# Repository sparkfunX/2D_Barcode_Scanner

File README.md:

2D Barcode Scanner Breakout
========================================

[*2D Barcode Scanner Breakout (SPX-16441)*](https://www.sparkfun.com/products/16441)

The DYScan DE2120 is one of the coolest little barcode scanners we've ever seen. This tiny "scan engine" will read 20 different barcode symbologies — both 1D and 2D! This is achieved by using a camera coupled with on-board image processing to identify and decode everything from UPC codes to QR codes. The module also features two LEDs: one for illumination and one to project the red line that you're used to seeing from laser-based scanners. 

This breakout board makes it easy to explore all of the capabilities of the DE2120 without dealing with finicky flat flex cables. The scanner's USB interface is exposed via the on-board USB-C connector. A buzzer and status LED are connected to the module through appropriate drive circuits and a pushbutton tactile switch is provided on the "trigger" pin. When you're ready to incorporate the module into your embedded project, you can leverage the 5 pin header for direct access to the TTL serial pins, power pins, and trigger input.

The module can be configured either by using the serial interface or by scanning command barcodes found in the datasheet.

Repository Contents
-------------------
* **/Hardware** - Eagle design files (.brd, .sch)

Documentation
--------------
* [Schematic](https://cdn.sparkfun.com/assets/3/8/9/6/0/2D_Barcode_Scanner.pdf)
* [Datasheet](https://cdn.sparkfun.com/assets/6/4/6/1/f/DY_SCAN_Specification-DE2120_1___2_.pdf)
* [Settings Manual](https://cdn.sparkfun.com/assets/b/5/0/e/e/DY_Scan_Setting_Manual-DE2120___19.4.6___.pdf)
* [Eagle Files](https://cdn.sparkfun.com/assets/2/d/f/7/b/2DBarcodeScanner.zip)

License Information
-------------------

This product is _**open source**_! 

Please review the LICENSE.md file for license information. 

If you have any questions or concerns on licensing, please contact technical support on our [SparkFun forums](https://forum.sparkfun.com/viewforum.php?f=152).

Distributed as-is; no warranty is given.

- Your friends at SparkFun.

_<COLLABORATION CREDIT>_

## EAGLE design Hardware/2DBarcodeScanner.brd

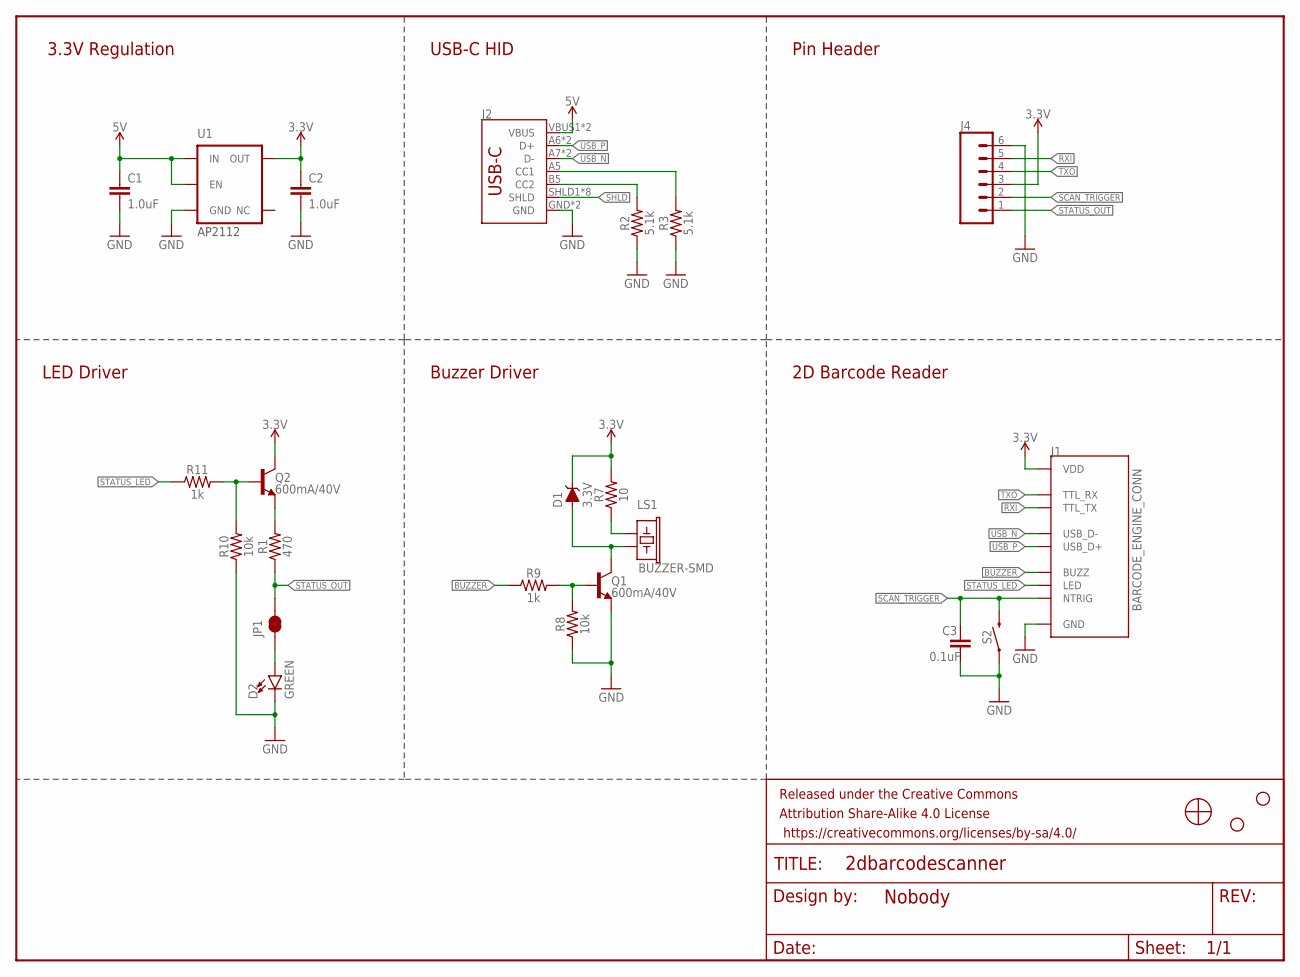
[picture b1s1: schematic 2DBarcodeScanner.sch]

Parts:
C1, C2: 1.0uF; 0603
C3: 0.1uF; 0603
D1: 3.3V; SOD-323
D2: GREEN; LED-0603
FRAME1: FRAME-LETTERNO_PACKAGE; DUMMY
H2, H3: STAND-OFF
J1: BARCODE_ENGINE_CONN; CONN_FPC_BOTTOM_12POS_.5MM_R/A
J2: USB_C2-LAYER; USB-C-16P
J4: CONN_06NO_SILK_FEMALE_PTH; 1X06_NO_SILK
JP1: JUMPER-SMT_2_NC_TRACE_SILK; SMT-JUMPER_2_NC_TRACE_SILK
LS1: BUZZER-SMD; BUZZER-CCV
Q1, Q2: 600mA/40V; SOT23-3
R1: 470; 0603
R2, R3: 5.1k; 0603
R7: 10; 0603
R8, R10: 10k; 0603
R9, R11: 1k; 0603
S2: MOMENTARY-SWITCH-SPST-SMD-5.2MM-TALL; TACTILE_SWITCH_SMD_5.2MM
U1: 3.3V; SOT23-5
U$1: BARCODE_SCANNER_MOUNT

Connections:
3.3V: C2.1, D1.C, J1.P$11 (VDD), J4.3, Q2.3 (C), R7.2, U1.5 (OUT)
5V: C1.1, J2.VBUS1 (VBUS), J2.VBUS2 (VBUS), U1.1 (IN), U1.3 (EN)
BUZZER: J1.P$4 (BUZZ), R9.1
CC3: J2.A5 (CC1), R3.2
CC4: J2.B5 (CC2), R2.2
GND: C1.2, C2.2, C3.2, D2.C, J1.P$10 (GND), J1.P$13 (GND), J1.P$14 (GND), J2.GND, J2.GND2 (GND), J4.6, Q1.2 (E), R2.1, R3.1, R8.1, R10.1, S2.1, U1.2 (GND)
unnamed: D1.A, LS1.- (2), Q1.3 (C)
unnamed: LS1.+ (1), R7.1
unnamed: Q2.2 (E), R1.2
unnamed: Q1.1 (B), R8.2, R9.2
unnamed: Q2.1 (B), R10.2, R11.2
unnamed: D2.A, JP1.1
RXI: J1.P$8 (TTL_TX), J4.5
SCAN_TRIGGER: C3.1, J1.P$1 (NTRIG), J4.2, S2.3 (2)
SHLD: J2.SHLD1 (SHLD), J2.SHLD2 (SHLD), J2.SHLD3 (SHLD), J2.SHLD4 (SHLD), J2.SHLD5 (SHLD), J2.SHLD6 (SHLD), J2.SHLD7 (SHLD), J2.SHLD8 (SHLD)
STATUS_LED: J1.P$3 (LED), R11.1
STATUS_OUT: J4.1, JP1.2, R1.1
TXO: J1.P$9 (TTL_RX), J4.4
USB_N: J1.P$7 (USB_D-), J2.A7 (D-), J2.B7 (D-)
USB_P: J1.P$6 (USB_D+), J2.A6 (D+), J2.B6 (D+)

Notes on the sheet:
3.3V Regulation
AP2112
Pin Header
2D Barcode Reader
LED Driver
Buzzer Driver
USB-C HID

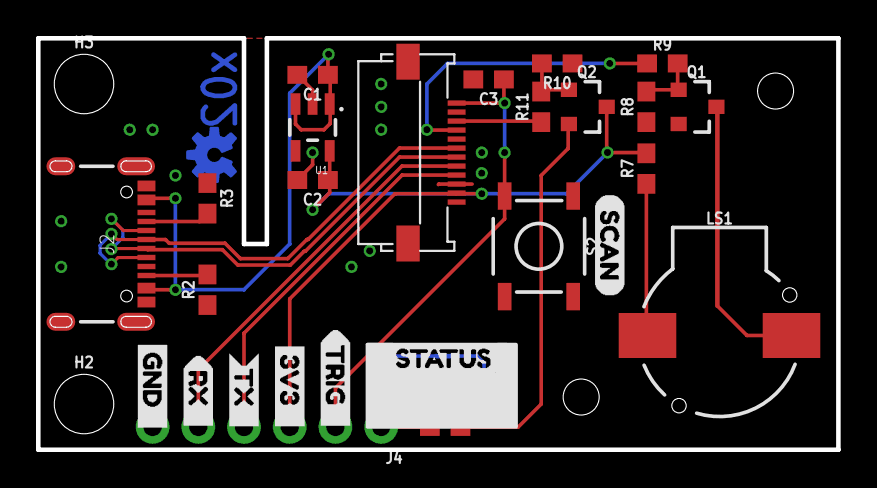
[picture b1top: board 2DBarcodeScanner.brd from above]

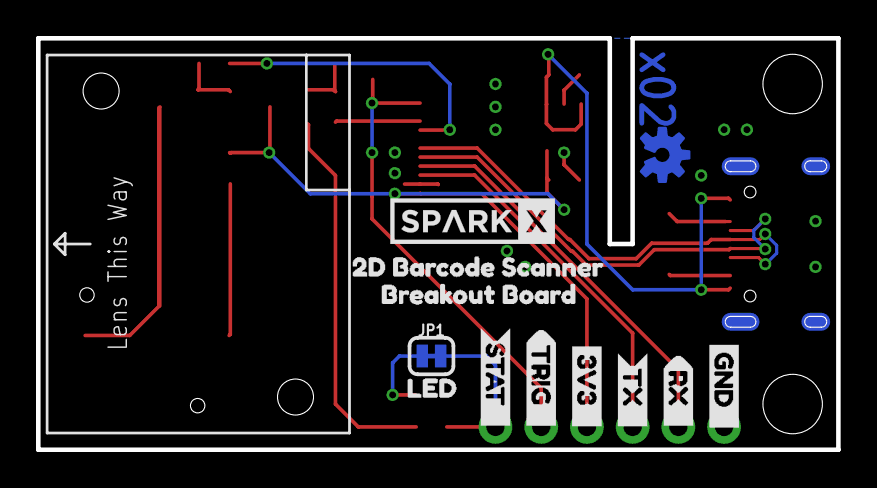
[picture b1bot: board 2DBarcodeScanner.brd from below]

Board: 2 copper layers, 44.5 x 22.9 mm, 43 parts (13 on the bottom side), 20 nets.

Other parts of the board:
U$2: STATUS3
U$3: STAT__5
U$4, U$5: TRIG__4
U$6, U$9: 3V3__3
U$7: SCAN4
U$8: LED0
U$10, U$11: TX__2
U$12, U$13: RX__1
U$14, U$15: GND__0
U$17: 2D_BARCODE_SCANNER0
U$18: BREAKOUT_BOARD1
U$20: SPARKX-MEDIUM
U$21: OSHW-LOGO-S_COPPER

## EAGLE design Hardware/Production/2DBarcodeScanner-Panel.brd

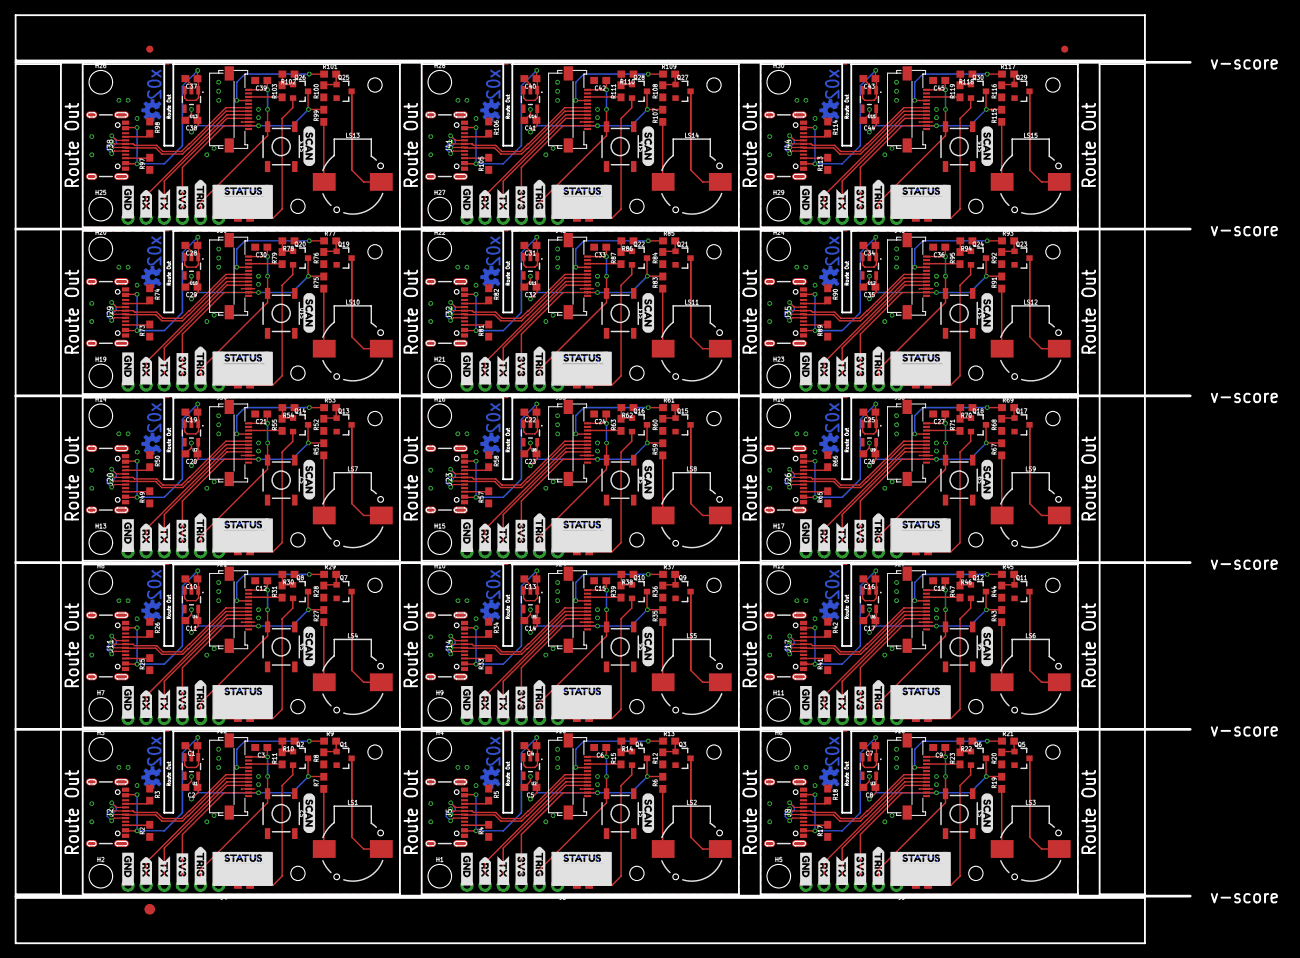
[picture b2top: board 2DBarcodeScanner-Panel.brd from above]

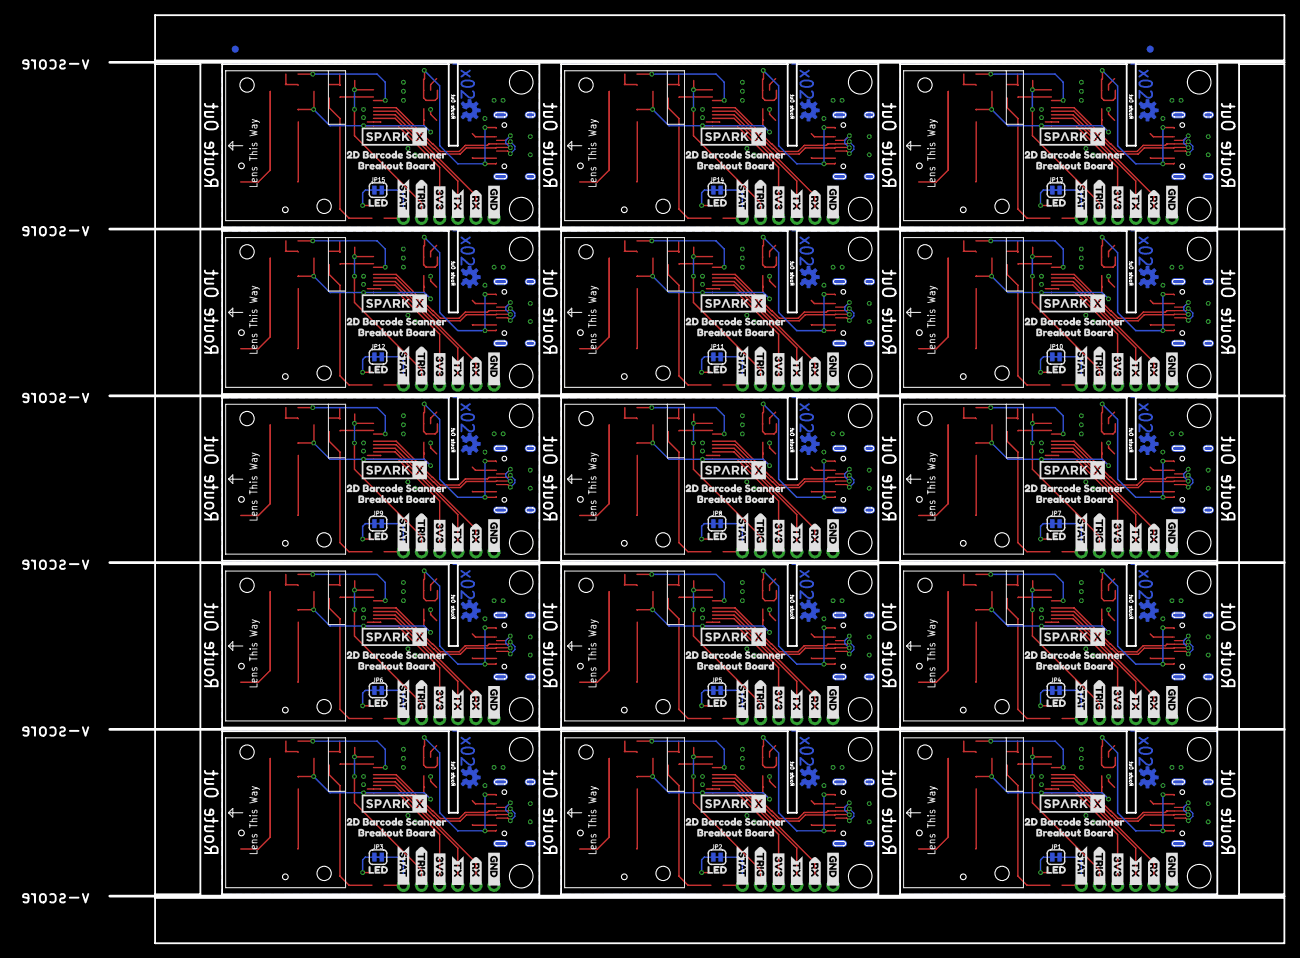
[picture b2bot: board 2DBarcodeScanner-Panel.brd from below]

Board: 2 copper layers, 177.8 x 129.9 mm, 650 parts (197 on the bottom side), 300 nets.

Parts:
C1, C2, C4, C5, C7, C8, C10, C11, C13, C14, C16, C17, C19, C20, C22, C23, C25, C26, C28, C29, C31, C32, C34, C35, C37, C38, C40, C41, C43, C44: 1.0uF; 0603
C3, C6, C9, C12, C15, C18, C21, C24, C27, C30, C33, C36, C39, C42, C45: 0.1uF; 0603
D1, D2, D3, D4, D5, D6, D7, D8, D9, D10, D11, D12, D13, D14, D15: GREEN; LED-0603
E$1, E$2, E$3, E$4: FIDUCIAL-1X2
E$5: FIDUCIAL-1.5X3
FRAME1, FRAME2, FRAME3, FRAME4, FRAME5, FRAME6, FRAME7, FRAME8, FRAME9, FRAME10, FRAME11, FRAME12, FRAME13, FRAME14, FRAME15: FRAME-LETTERNO_PACKAGE; DUMMY
H1, H2, H3, H4, H5, H6, H7, H8, H9, H10, H11, H12, H13, H14, H15, H16, H17, H18, H19, H20, H21, H22, H23, H24, H25, H26, H27, H28, H29, H30: STAND-OFF
J1, J3, J7, J10, J13, J16, J19, J22, J25, J28, J31, J34, J37, J40, J43: BARCODE_ENGINE_CONN; CONN_FPC_BOTTOM_12POS_.5MM_R/A
J2, J5, J8, J11, J14, J17, J20, J23, J26, J29, J32, J35, J38, J41, J44: USB-C-16P
J4, J6, J9, J12, J15, J18, J21, J24, J27, J30, J33, J36, J39, J42, J45: 1X06_NO_SILK
JP1, JP2, JP3, JP4, JP5, JP6, JP7, JP8, JP9, JP10, JP11, JP12, JP13, JP14, JP15: JUMPER-SMT_2_NC_TRACE_SILK; SMT-JUMPER_2_NC_TRACE_SILK
LS1, LS2, LS3, LS4, LS5, LS6, LS7, LS8, LS9, LS10, LS11, LS12, LS13, LS14, LS15: BUZZER-SMD; BUZZER-CCV
Q1, Q2, Q3, Q4, Q5, Q6, Q7, Q8, Q9, Q10, Q11, Q12, Q13, Q14, Q15, Q16, Q17, Q18, Q19, Q20, Q21, Q22, Q23, Q24, Q25, Q26, Q27, Q28, Q29, Q30: 600mA/40V; SOT23-3
R1, R16, R24, R32, R40, R48, R56, R64, R72, R80, R88, R96, R104, R112, R120: 470; 0603
R2, R3, R4, R5, R17, R18, R25, R26, R33, R34, R41, R42, R49, R50, R57, R58, R65, R66, R73, R74, R81, R82, R89, R90, R97, R98, R105, R106, R113, R114: 5.1k; 0603
R6, R7, R19, R27, R35, R43, R51, R59, R67, R75, R83, R91, R99, R107, R115: 10; 0603
R8, R10, R12, R14, R20, R22, R28, R30, R36, R38, R44, R46, R52, R54, R60, R62, R68, R70, R76, R78, R84, R86, R92, R94, R100, R102, R108, R110, R116, R118: 10k; 0603
R9, R11, R13, R15, R21, R23, R29, R31, R37, R39, R45, R47, R53, R55, R61, R63, R69, R71, R77, R79, R85, R87, R93, R95, R101, R103, R109, R111, R117, R119: 1k; 0603
S1, S2, S3, S4, S5, S6, S7, S8, S9, S10, S11, S12, S13, S14, S15: MOMENTARY-SWITCH-SPST-SMD-5.2MM-TALL; TACTILE_SWITCH_SMD_5.2MM
U1, U2, U3, U4, U5, U6, U7, U8, U9, U10, U11, U12, U13, U14, U15: 3.3V; SOT23-5
U$1, U$16, U$39, U$58, U$77, U$96, U$115, U$134, U$153, U$172, U$191, U$210, U$229, U$248, U$267: BARCODE_SCANNER_MOUNT
U$2, U$37, U$56, U$75, U$94, U$113, U$132, U$151, U$170, U$189, U$208, U$227, U$246, U$265, U$284: STATUS3
U$3, U$26, U$45, U$64, U$83, U$102, U$121, U$140, U$159, U$178, U$197, U$216, U$235, U$254, U$273: STAT__5
U$4, U$5, U$27, U$28, U$46, U$47, U$65, U$66, U$84, U$85, U$103, U$104, U$122, U$123, U$141, U$142, U$160, U$161, U$179, U$180, U$198, U$199, U$217, U$218, U$236, U$237, U$255, U$256, U$274, U$275: TRIG__4
U$6, U$9, U$29, U$30, U$48, U$49, U$67, U$68, U$86, U$87, U$105, U$106, U$124, U$125, U$143, U$144, U$162, U$163, U$181, U$182, U$200, U$201, U$219, U$220, U$238, U$239, U$257, U$258, U$276, U$277: 3V3__3
U$7, U$19, U$40, U$59, U$78, U$97, U$116, U$135, U$154, U$173, U$192, U$211, U$230, U$249, U$268: SCAN4
U$8, U$38, U$57, U$76, U$95, U$114, U$133, U$152, U$171, U$190, U$209, U$228, U$247, U$266, U$285: LED0
U$10, U$11, U$31, U$32, U$50, U$51, U$69, U$70, U$88, U$89, U$107, U$108, U$126, U$127, U$145, U$146, U$164, U$165, U$183, U$184, U$202, U$203, U$221, U$222, U$240, U$241, U$259, U$260, U$278, U$279: TX__2
U$12, U$13, U$33, U$34, U$52, U$53, U$71, U$72, U$90, U$91, U$109, U$110, U$128, U$129, U$147, U$148, U$166, U$167, U$185, U$186, U$204, U$205, U$223, U$224, U$242, U$243, U$261, U$262, U$280, U$281: RX__1
U$14, U$15, U$35, U$36, U$54, U$55, U$73, U$74, U$92, U$93, U$111, U$112, U$130, U$131, U$149, U$150, U$168, U$169, U$187, U$188, U$206, U$207, U$225, U$226, U$244, U$245, U$263, U$264, U$282, U$283: GND__0
U$17, U$22, U$41, U$60, U$79, U$98, U$117, U$136, U$155, U$174, U$193, U$212, U$231, U$250, U$269: 2D_BARCODE_SCANNER0
U$18, U$23, U$42, U$61, U$80, U$99, U$118, U$137, U$156, U$175, U$194, U$213, U$232, U$251, U$270: BREAKOUT_BOARD1
U$20, U$24, U$43, U$62, U$81, U$100, U$119, U$138, U$157, U$176, U$195, U$214, U$233, U$252, U$271: SPARKX-MEDIUM
U$21, U$25, U$44, U$63, U$82, U$101, U$120, U$139, U$158, U$177, U$196, U$215, U$234, U$253, U$272: OSHW-LOGO-S_COPPER

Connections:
3.3V: C2.1, J1.P$11, J4.3, Q2.3, R7.2, U1.5
3.3V1: C5.1, J3.P$11, J6.3, Q4.3, R6.2, U2.5
3.3V2: C8.1, J7.P$11, J9.3, Q6.3, R19.2, U3.5
3.3V3: C11.1, J10.P$11, J12.3, Q8.3, R27.2, U4.5
3.3V4: C14.1, J13.P$11, J15.3, Q10.3, R35.2, U5.5
3.3V5: C17.1, J16.P$11, J18.3, Q12.3, R43.2, U6.5
3.3V6: C20.1, J19.P$11, J21.3, Q14.3, R51.2, U7.5
3.3V7: C23.1, J22.P$11, J24.3, Q16.3, R59.2, U8.5
3.3V8: C26.1, J25.P$11, J27.3, Q18.3, R67.2, U9.5
3.3V9: C29.1, J28.P$11, J30.3, Q20.3, R75.2, U10.5
3.3V10: C32.1, J31.P$11, J33.3, Q22.3, R83.2, U11.5
3.3V11: C35.1, J34.P$11, J36.3, Q24.3, R91.2, U12.5
3.3V12: C38.1, J37.P$11, J39.3, Q26.3, R99.2, U13.5
3.3V13: C41.1, J40.P$11, J42.3, Q28.3, R107.2, U14.5
3.3V14: C44.1, J43.P$11, J45.3, Q30.3, R115.2, U15.5
5V: C1.1, J2.VBUS1, J2.VBUS2, U1.1, U1.3
5V1: C4.1, J5.VBUS1, J5.VBUS2, U2.1, U2.3
5V2: C7.1, J8.VBUS1, J8.VBUS2, U3.1, U3.3
5V3: C10.1, J11.VBUS1, J11.VBUS2, U4.1, U4.3
5V4: C13.1, J14.VBUS1, J14.VBUS2, U5.1, U5.3
5V5: C16.1, J17.VBUS1, J17.VBUS2, U6.1, U6.3
5V6: C19.1, J20.VBUS1, J20.VBUS2, U7.1, U7.3
5V7: C22.1, J23.VBUS1, J23.VBUS2, U8.1, U8.3
5V8: C25.1, J26.VBUS1, J26.VBUS2, U9.1, U9.3
5V9: C28.1, J29.VBUS1, J29.VBUS2, U10.1, U10.3
5V10: C31.1, J32.VBUS1, J32.VBUS2, U11.1, U11.3
5V11: C34.1, J35.VBUS1, J35.VBUS2, U12.1, U12.3
5V12: C37.1, J38.VBUS1, J38.VBUS2, U13.1, U13.3
5V13: C40.1, J41.VBUS1, J41.VBUS2, U14.1, U14.3
5V14: C43.1, J44.VBUS1, J44.VBUS2, U15.1, U15.3
BUZZER: J1.P$4, R9.1
BUZZER1: J3.P$4, R13.1
BUZZER2: J7.P$4, R21.1
BUZZER3: J10.P$4, R29.1
BUZZER4: J13.P$4, R37.1
BUZZER5: J16.P$4, R45.1
BUZZER6: J19.P$4, R53.1
BUZZER7: J22.P$4, R61.1
BUZZER8: J25.P$4, R69.1
BUZZER9: J28.P$4, R77.1
BUZZER10: J31.P$4, R85.1
BUZZER11: J34.P$4, R93.1
BUZZER12: J37.P$4, R101.1
BUZZER13: J40.P$4, R109.1
BUZZER14: J43.P$4, R117.1
CC1: J5.A5, R5.2
CC2: J5.B5, R4.2
CC3: J2.A5, R3.2
CC4: J2.B5, R2.2
CC5: J8.A5, R18.2
CC6: J8.B5, R17.2
CC7: J11.A5, R26.2
CC8: J11.B5, R25.2
CC9: J14.A5, R34.2
CC10: J14.B5, R33.2
CC11: J17.A5, R42.2
CC12: J17.B5, R41.2
CC13: J20.A5, R50.2
CC14: J20.B5, R49.2
CC15: J23.A5, R58.2
CC16: J23.B5, R57.2
CC17: J26.A5, R66.2
CC18: J26.B5, R65.2
CC19: J29.A5, R74.2
CC20: J29.B5, R73.2
CC21: J32.A5, R82.2
CC22: J32.B5, R81.2
CC23: J35.A5, R90.2
CC24: J35.B5, R89.2
CC25: J38.A5, R98.2
CC26: J38.B5, R97.2
CC27: J41.A5, R106.2
CC28: J41.B5, R105.2
CC29: J44.A5, R114.2
CC30: J44.B5, R113.2
GND: C1.2, C2.2, C3.2, D2.C, J1.P$10, J1.P$13, J1.P$14, J2.GND, J2.GND2, J4.6, Q1.2, R2.1, R3.1, R8.1, R10.1, S2.1, U1.2
GND1: C4.2, C5.2, C6.2, D1.C, J3.P$10, J3.P$13, J3.P$14, J5.GND, J5.GND2, J6.6, Q3.2, R4.1, R5.1, R12.1, R14.1, S1.1, U2.2
GND2: C7.2, C8.2, C9.2, D3.C, J7.P$10, J7.P$13, J7.P$14, J8.GND, J8.GND2, J9.6, Q5.2, R17.1, R18.1, R20.1, R22.1, S3.1, U3.2
GND3: C10.2, C11.2, C12.2, D4.C, J10.P$10, J10.P$13, J10.P$14, J11.GND, J11.GND2, J12.6, Q7.2, R25.1, R26.1, R28.1, R30.1, S4.1, U4.2
GND4: C13.2, C14.2, C15.2, D5.C, J13.P$10, J13.P$13, J13.P$14, J14.GND, J14.GND2, J15.6, Q9.2, R33.1, R34.1, R36.1, R38.1, S5.1, U5.2
GND5: C16.2, C17.2, C18.2, D6.C, J16.P$10, J16.P$13, J16.P$14, J17.GND, J17.GND2, J18.6, Q11.2, R41.1, R42.1, R44.1, R46.1, S6.1, U6.2
GND6: C19.2, C20.2, C21.2, D7.C, J19.P$10, J19.P$13, J19.P$14, J20.GND, J20.GND2, J21.6, Q13.2, R49.1, R50.1, R52.1, R54.1, S7.1, U7.2
GND7: C22.2, C23.2, C24.2, D8.C, J22.P$10, J22.P$13, J22.P$14, J23.GND, J23.GND2, J24.6, Q15.2, R57.1, R58.1, R60.1, R62.1, S8.1, U8.2
GND8: C25.2, C26.2, C27.2, D9.C, J25.P$10, J25.P$13, J25.P$14, J26.GND, J26.GND2, J27.6, Q17.2, R65.1, R66.1, R68.1, R70.1, S9.1, U9.2
GND9: C28.2, C29.2, C30.2, D10.C, J28.P$10, J28.P$13, J28.P$14, J29.GND, J29.GND2, J30.6, Q19.2, R73.1, R74.1, R76.1, R78.1, S10.1, U10.2
GND10: C31.2, C32.2, C33.2, D11.C, J31.P$10, J31.P$13, J31.P$14, J32.GND, J32.GND2, J33.6, Q21.2, R81.1, R82.1, R84.1, R86.1, S11.1, U11.2
GND11: C34.2, C35.2, C36.2, D12.C, J34.P$10, J34.P$13, J34.P$14, J35.GND, J35.GND2, J36.6, Q23.2, R89.1, R90.1, R92.1, R94.1, S12.1, U12.2
GND12: C37.2, C38.2, C39.2, D13.C, J37.P$10, J37.P$13, J37.P$14, J38.GND, J38.GND2, J39.6, Q25.2, R97.1, R98.1, R100.1, R102.1, S13.1, U13.2
GND13: C40.2, C41.2, C42.2, D14.C, J40.P$10, J40.P$13, J40.P$14, J41.GND, J41.GND2, J42.6, Q27.2, R105.1, R106.1, R108.1, R110.1, S14.1, U14.2
GND14: C43.2, C44.2, C45.2, D15.C, J43.P$10, J43.P$13, J43.P$14, J44.GND, J44.GND2, J45.6, Q29.2, R113.1, R114.1, R116.1, R118.1, S15.1, U15.2
unnamed: LS2.-, Q3.3
unnamed: LS1.-, Q1.3
unnamed: LS1.+, R7.1
unnamed: Q2.2, R1.2
unnamed: Q1.1, R8.2, R9.2
unnamed: LS2.+, R6.1
unnamed: Q2.1, R10.2, R11.2
unnamed: D2.A, JP1.1
unnamed: Q3.1, R12.2, R13.2
unnamed: Q4.2, R16.2
unnamed: Q4.1, R14.2, R15.2
unnamed: D1.A, JP2.1
unnamed: LS3.-, Q5.3
unnamed: LS3.+, R19.1
unnamed: Q5.1, R20.2, R21.2
unnamed: Q6.2, R24.2
unnamed: Q6.1, R22.2, R23.2
unnamed: D3.A, JP3.1
unnamed: LS4.-, Q7.3
unnamed: LS4.+, R27.1
unnamed: Q7.1, R28.2, R29.2
unnamed: Q8.2, R32.2
unnamed: Q8.1, R30.2, R31.2
unnamed: D4.A, JP4.1
unnamed: LS5.-, Q9.3
unnamed: LS5.+, R35.1
unnamed: Q9.1, R36.2, R37.2
unnamed: Q10.2, R40.2
unnamed: Q10.1, R38.2, R39.2
unnamed: D5.A, JP5.1
unnamed: LS6.-, Q11.3
unnamed: LS6.+, R43.1
unnamed: Q11.1, R44.2, R45.2
unnamed: Q12.2, R48.2
unnamed: Q12.1, R46.2, R47.2
unnamed: D6.A, JP6.1
unnamed: LS7.-, Q13.3
unnamed: LS7.+, R51.1
unnamed: Q13.1, R52.2, R53.2
unnamed: Q14.2, R56.2
unnamed: Q14.1, R54.2, R55.2
unnamed: D7.A, JP7.1
unnamed: LS8.-, Q15.3
unnamed: LS8.+, R59.1
unnamed: Q15.1, R60.2, R61.2
unnamed: Q16.2, R64.2
unnamed: Q16.1, R62.2, R63.2
unnamed: D8.A, JP8.1
unnamed: LS9.-, Q17.3
unnamed: LS9.+, R67.1
unnamed: Q17.1, R68.2, R69.2
unnamed: Q18.2, R72.2
unnamed: Q18.1, R70.2, R71.2
unnamed: D9.A, JP9.1
unnamed: LS10.-, Q19.3
unnamed: LS10.+, R75.1
unnamed: Q19.1, R76.2, R77.2
unnamed: Q20.2, R80.2
unnamed: Q20.1, R78.2, R79.2
unnamed: D10.A, JP10.1
unnamed: LS11.-, Q21.3
unnamed: LS11.+, R83.1
unnamed: Q21.1, R84.2, R85.2
unnamed: Q22.2, R88.2
unnamed: Q22.1, R86.2, R87.2
unnamed: D11.A, JP11.1
unnamed: LS12.-, Q23.3
unnamed: LS12.+, R91.1
unnamed: Q23.1, R92.2, R93.2
unnamed: Q24.2, R96.2
unnamed: Q24.1, R94.2, R95.2
unnamed: D12.A, JP12.1
unnamed: LS13.-, Q25.3
unnamed: LS13.+, R99.1
unnamed: Q25.1, R100.2, R101.2
unnamed: Q26.2, R104.2
unnamed: Q26.1, R102.2, R103.2
unnamed: D13.A, JP13.1
unnamed: LS14.-, Q27.3
unnamed: LS14.+, R107.1
unnamed: Q27.1, R108.2, R109.2
unnamed: Q28.2, R112.2
unnamed: Q28.1, R110.2, R111.2
unnamed: D14.A, JP14.1
unnamed: LS15.-, Q29.3
unnamed: LS15.+, R115.1
unnamed: Q29.1, R116.2, R117.2
unnamed: Q30.2, R120.2
unnamed: Q30.1, R118.2, R119.2
unnamed: D15.A, JP15.1
RXI: J1.P$8, J4.5
RXI1: J3.P$8, J6.5
RXI2: J7.P$8, J9.5
RXI3: J10.P$8, J12.5
RXI4: J13.P$8, J15.5
RXI5: J16.P$8, J18.5
RXI6: J19.P$8, J21.5
RXI7: J22.P$8, J24.5
RXI8: J25.P$8, J27.5
RXI9: J28.P$8, J30.5
RXI10: J31.P$8, J33.5
RXI11: J34.P$8, J36.5
RXI12: J37.P$8, J39.5
RXI13: J40.P$8, J42.5
RXI14: J43.P$8, J45.5
SCAN_TRIGGER: C3.1, J1.P$1, J4.2, S2.3
SCAN_TRIGGER1: C6.1, J3.P$1, J6.2, S1.3
SCAN_TRIGGER2: C9.1, J7.P$1, J9.2, S3.3
SCAN_TRIGGER3: C12.1, J10.P$1, J12.2, S4.3
SCAN_TRIGGER4: C15.1, J13.P$1, J15.2, S5.3
SCAN_TRIGGER5: C18.1, J16.P$1, J18.2, S6.3
SCAN_TRIGGER6: C21.1, J19.P$1, J21.2, S7.3
SCAN_TRIGGER7: C24.1, J22.P$1, J24.2, S8.3
SCAN_TRIGGER8: C27.1, J25.P$1, J27.2, S9.3
SCAN_TRIGGER9: C30.1, J28.P$1, J30.2, S10.3
SCAN_TRIGGER10: C33.1, J31.P$1, J33.2, S11.3
SCAN_TRIGGER11: C36.1, J34.P$1, J36.2, S12.3
SCAN_TRIGGER12: C39.1, J37.P$1, J39.2, S13.3
SCAN_TRIGGER13: C42.1, J40.P$1, J42.2, S14.3
SCAN_TRIGGER14: C45.1, J43.P$1, J45.2, S15.3
SHLD: J2.SHLD1, J2.SHLD2, J2.SHLD3, J2.SHLD4, J2.SHLD5, J2.SHLD6, J2.SHLD7, J2.SHLD8
SHLD1: J5.SHLD1, J5.SHLD2, J5.SHLD3, J5.SHLD4, J5.SHLD5, J5.SHLD6, J5.SHLD7, J5.SHLD8
SHLD2: J8.SHLD1, J8.SHLD2, J8.SHLD3, J8.SHLD4, J8.SHLD5, J8.SHLD6, J8.SHLD7, J8.SHLD8
SHLD3: J11.SHLD1, J11.SHLD2, J11.SHLD3, J11.SHLD4, J11.SHLD5, J11.SHLD6, J11.SHLD7, J11.SHLD8
SHLD4: J14.SHLD1, J14.SHLD2, J14.SHLD3, J14.SHLD4, J14.SHLD5, J14.SHLD6, J14.SHLD7, J14.SHLD8
SHLD5: J17.SHLD1, J17.SHLD2, J17.SHLD3, J17.SHLD4, J17.SHLD5, J17.SHLD6, J17.SHLD7, J17.SHLD8
SHLD6: J20.SHLD1, J20.SHLD2, J20.SHLD3, J20.SHLD4, J20.SHLD5, J20.SHLD6, J20.SHLD7, J20.SHLD8
SHLD7: J23.SHLD1, J23.SHLD2, J23.SHLD3, J23.SHLD4, J23.SHLD5, J23.SHLD6, J23.SHLD7, J23.SHLD8
SHLD8: J26.SHLD1, J26.SHLD2, J26.SHLD3, J26.SHLD4, J26.SHLD5, J26.SHLD6, J26.SHLD7, J26.SHLD8
SHLD9: J29.SHLD1, J29.SHLD2, J29.SHLD3, J29.SHLD4, J29.SHLD5, J29.SHLD6, J29.SHLD7, J29.SHLD8
SHLD10: J32.SHLD1, J32.SHLD2, J32.SHLD3, J32.SHLD4, J32.SHLD5, J32.SHLD6, J32.SHLD7, J32.SHLD8
SHLD11: J35.SHLD1, J35.SHLD2, J35.SHLD3, J35.SHLD4, J35.SHLD5, J35.SHLD6, J35.SHLD7, J35.SHLD8
SHLD12: J38.SHLD1, J38.SHLD2, J38.SHLD3, J38.SHLD4, J38.SHLD5, J38.SHLD6, J38.SHLD7, J38.SHLD8
SHLD13: J41.SHLD1, J41.SHLD2, J41.SHLD3, J41.SHLD4, J41.SHLD5, J41.SHLD6, J41.SHLD7, J41.SHLD8
SHLD14: J44.SHLD1, J44.SHLD2, J44.SHLD3, J44.SHLD4, J44.SHLD5, J44.SHLD6, J44.SHLD7, J44.SHLD8
STATUS_LED: J1.P$3, R11.1
STATUS_LED1: J3.P$3, R15.1
STATUS_LED2: J7.P$3, R23.1
STATUS_LED3: J10.P$3, R31.1
STATUS_LED4: J13.P$3, R39.1
STATUS_LED5: J16.P$3, R47.1
STATUS_LED6: J19.P$3, R55.1
STATUS_LED7: J22.P$3, R63.1
STATUS_LED8: J25.P$3, R71.1
STATUS_LED9: J28.P$3, R79.1
STATUS_LED10: J31.P$3, R87.1
STATUS_LED11: J34.P$3, R95.1
STATUS_LED12: J37.P$3, R103.1
STATUS_LED13: J40.P$3, R111.1
STATUS_LED14: J43.P$3, R119.1
STATUS_OUT: J4.1, JP1.2, R1.1
STATUS_OUT1: J6.1, JP2.2, R16.1
STATUS_OUT2: J9.1, JP3.2, R24.1
STATUS_OUT3: J12.1, JP4.2, R32.1
STATUS_OUT4: J15.1, JP5.2, R40.1
STATUS_OUT5: J18.1, JP6.2, R48.1
STATUS_OUT6: J21.1, JP7.2, R56.1
STATUS_OUT7: J24.1, JP8.2, R64.1
STATUS_OUT8: J27.1, JP9.2, R72.1
STATUS_OUT9: J30.1, JP10.2, R80.1
STATUS_OUT10: J33.1, JP11.2, R88.1
STATUS_OUT11: J36.1, JP12.2, R96.1
STATUS_OUT12: J39.1, JP13.2, R104.1
STATUS_OUT13: J42.1, JP14.2, R112.1
STATUS_OUT14: J45.1, JP15.2, R120.1
TXO: J1.P$9, J4.4
TXO1: J3.P$9, J6.4
TXO2: J7.P$9, J9.4
TXO3: J10.P$9, J12.4
TXO4: J13.P$9, J15.4
TXO5: J16.P$9, J18.4
TXO6: J19.P$9, J21.4
TXO7: J22.P$9, J24.4
TXO8: J25.P$9, J27.4
TXO9: J28.P$9, J30.4
TXO10: J31.P$9, J33.4
TXO11: J34.P$9, J36.4
TXO12: J37.P$9, J39.4
TXO13: J40.P$9, J42.4
TXO14: J43.P$9, J45.4
USB_N: J1.P$7, J2.A7, J2.B7
USB_N1: J3.P$7, J5.A7, J5.B7
USB_N2: J7.P$7, J8.A7, J8.B7
USB_N3: J10.P$7, J11.A7, J11.B7
USB_N4: J13.P$7, J14.A7, J14.B7
USB_N5: J16.P$7, J17.A7, J17.B7
USB_N6: J19.P$7, J20.A7, J20.B7
USB_N7: J22.P$7, J23.A7, J23.B7
USB_N8: J25.P$7, J26.A7, J26.B7
USB_N9: J28.P$7, J29.A7, J29.B7
USB_N10: J31.P$7, J32.A7, J32.B7
USB_N11: J34.P$7, J35.A7, J35.B7
USB_N12: J37.P$7, J38.A7, J38.B7
USB_N13: J40.P$7, J41.A7, J41.B7
USB_N14: J43.P$7, J44.A7, J44.B7
USB_P: J1.P$6, J2.A6, J2.B6
USB_P1: J3.P$6, J5.A6, J5.B6
USB_P2: J7.P$6, J8.A6, J8.B6
USB_P3: J10.P$6, J11.A6, J11.B6
USB_P4: J13.P$6, J14.A6, J14.B6
USB_P5: J16.P$6, J17.A6, J17.B6
USB_P6: J19.P$6, J20.A6, J20.B6
USB_P7: J22.P$6, J23.A6, J23.B6
USB_P8: J25.P$6, J26.A6, J26.B6
USB_P9: J28.P$6, J29.A6, J29.B6
USB_P10: J31.P$6, J32.A6, J32.B6
USB_P11: J34.P$6, J35.A6, J35.B6
USB_P12: J37.P$6, J38.A6, J38.B6
USB_P13: J40.P$6, J41.A6, J41.B6
USB_P14: J43.P$6, J44.A6, J44.B6

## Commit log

2019-12-13 x01 panels ordered
2020-02-27 Cleaning up backup files
2020-03-12 Version x02
2020-03-12 Forgot to pull that stupid diode
2020-03-12 Adding panel files x02
2020-04-02 cleaning up some temp files
2020-11-20 license and readme image
    added license and added an image to README

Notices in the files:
parts and their libraries:
SparkFun-Capacitors: Licensing: Creative Commons ShareAlike 4.0 International - https://creativecommons.org/licenses/by-sa/4.0
SparkFun-Aesthetics: Released under the Creative Commons Attribution Share-Alike 4.0 License
SparkFun-Aesthetics: https://creativecommons.org/licenses/by-sa/4.0
